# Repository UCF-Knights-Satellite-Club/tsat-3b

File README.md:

# tsat-3b
TSat-3B repository containing all kicads and guided parafoil descent code

- [`FlightController/`](FlightController/) - ESP32 guided parafoil flight controller (Arduino sketch). See its README.
- [`PowerDistributionBoard/`](PowerDistributionBoard/) - power distribution board (KiCad 10): schematic, PCB, Gerbers, BOM.

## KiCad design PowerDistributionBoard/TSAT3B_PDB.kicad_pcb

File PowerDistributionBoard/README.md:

# TSat-3B Power Distribution Board

<p align="center">
  <b>Rev B: review draft</b> &nbsp;·&nbsp; 55 × 40 mm &nbsp;·&nbsp; 2-layer, 1.6 mm &nbsp;·&nbsp; KiCad 10
</p>

This board takes the battery and makes every rail TSat-3B needs. It powers the flight computer, the radio, the GPS, the IMU,
the SD card and the parafoil servo, and it switches the cutter channel.

| Top | Bottom |
|:---:|:---:|
|  |  |

📄 **Schematic:** [PDF](docs/TSAT3B_PDB_schematic.pdf) · [SVG](docs/TSAT3B_PDB_schematic.svg)
&nbsp;&nbsp;🧾 **BOM:** [CSV](bom/TSAT3B_PDB_BOM.csv)
&nbsp;&nbsp;🏭 **Fabrication:** [Gerbers + drill (zip)](fabrication/TSAT3B_PDB_gerbers.zip)

## Power tree

```
 Battery (J1, XT30)
   │
   ├─ Q3 AO4407A P-MOSFET load switch ◄── SW1 slide switch (gate control only, R12/R13)
   │
   └─ D1 SS54 reverse-polarity diode ──► VBUS
        │
        ├─ U1 SY8105 buck ───────► +5V   (73.2k / 10k  → 4.99 V)
        │     └─ U3 TLV1117LV33 ─► +3V3
        │
        ├─ U2 SY8105 buck ───────► VSERVO (73.2k / 8.2k → 5.96 V)
        │
        └─ J2 ARM LINK jumper ───► CUT_PWR ──► J11 cutter (Q1 AO3400A low-side switch)
```

Each rail (+5V, +3V3, VSERVO) has a green indicator LED.

## Connectors

| Ref | Name | Pins | Notes |
|---|---|---|---|
| J1 | BATTERY | XT30 | Battery input |
| J2 | ARM LINK | 2 × 2.54 mm | Jumper links VBUS → CUT_PWR to arm the cutter |
| J3 | PICO | +5V, GND | |
| J4 | LoRa | +3V3, GND | |
| J5 | GPS | +3V3, GND | |
| J6 | IMU | +3V3, GND | |
| J7 | SD CARD | +3V3, GND | |
| J8 | SERVO 1 | VSERVO, PWM, GND | JST PH 3-pin |
| J9 | ESP32 interface | +5V, GND, CUT1_CMD, SERVO1_PWM | 4 × 2.54 mm |
| J11 | CUTTER 1 | CUT_PWR, switched drain | XT30 |

## Bill of materials

42 parts, 25 line items. MPNs are in the [BOM CSV](bom/TSAT3B_PDB_BOM.csv).

| Qty | Refs | Part | Value / MPN |
|---:|---|---|---|
| 2 | U1, U2 | Buck regulator, Silergy | SY8105IADC |
| 1 | U3 | 3.3 V LDO, TI | TLV1117LV33DCYR |
| 1 | Q3 | P-MOSFET load switch, AOS | AO4407A |
| 1 | Q1 | N-MOSFET cutter switch, AOS | AO3400A |
| 1 | D1 | Schottky diode | SS54SMB |
| 2 | L1, L2 | Inductor, TDK | 2.2 µH SPM5030VT-2R2M-D |
| 6 | C1, C2, C4, C6–C8 | Capacitor 0805 | 22 µF 25 V |
| 3 | C3, C5, C9 | Capacitor 0603 | 100 nF 50 V |
| 11 | R1–R9, R12, R13 | Resistors 0603 | 73.2k, 10k, 8.2k, 1k, 100R |
| 3 | D2–D4 | LED 0603 | Green |
| 1 | SW1 | Slide switch | MSS22D18G2 |
| 2 | J1, J11 | Connector | XT30UPB-M |
| 8 | J2–J9 | Headers | 2.54 mm / JST PH |

## Repository layout

```
PowerDistributionBoard/
├── TSAT3B_PDB.kicad_pro / .kicad_sch / .kicad_pcb   KiCad 10 project
├── TSAT3B.kicad_sym, TSAT3B.pretty/                 project symbol + footprint library
├── fp-lib-table, sym-lib-table                      point at the local library (${KIPRJMOD})
├── fabrication/                                     Gerbers, drill files, job file, zip
├── bom/                                             BOM (CSV)
└── docs/                                            schematic PDF/SVG and 3D renders
```

Open `TSAT3B_PDB.kicad_pro` in **KiCad 10 or newer**; KiCad 9 can't read these files. The custom parts in
`TSAT3B.pretty` (XT30, slide switch, inductors, SY8105) have no 3D models yet, so they show as bare pads in the renders.

## Status: open items before fabrication

Rev B is still a **review draft**. These come from the review notes in the schematic:

- [ ] Battery voltage/specification. The design assumes a supply that suits the 6 V buck and the switch's ≤12 V rating.
- [ ] Cutter: resistance/current, pulse duration and Q1 thermal/SOA check.
- [ ] Q3 and D1 current, inrush and dissipation, once battery and load data are known.
- [ ] VSERVO at 5.96 V: confirm it suits the servos.
- [ ] Verify land patterns: SY8105 (TSOT23-6), TDK inductor, XT30 (also polarity), and the slide switch contacts.
- [ ] Confirm harness polarity on all 2-pin headers, and the servo pin order (1 VSERVO, 2 PWM, 3 GND).
- [ ] Arming-link topology (VBUS → CUT_PWR): verify against the source design.
- [ ] Cross-check with the flight code: the parafoil controller in [`../FlightController`](../FlightController) drives
      **two** winch servos (left and right lines). This board has one servo header (J8) and one PWM line on J9.

Check results (KiCad 10.0.7):
- **DRC:** 0 unconnected pads and no clearance errors.
- **Parity:** the 4 mounting holes exist only on the PCB.
- **ERC:** 3 "power pin not driven" errors, which usually just need `PWR_FLAG` symbols on GND / VBAT_RAW / VBUS.

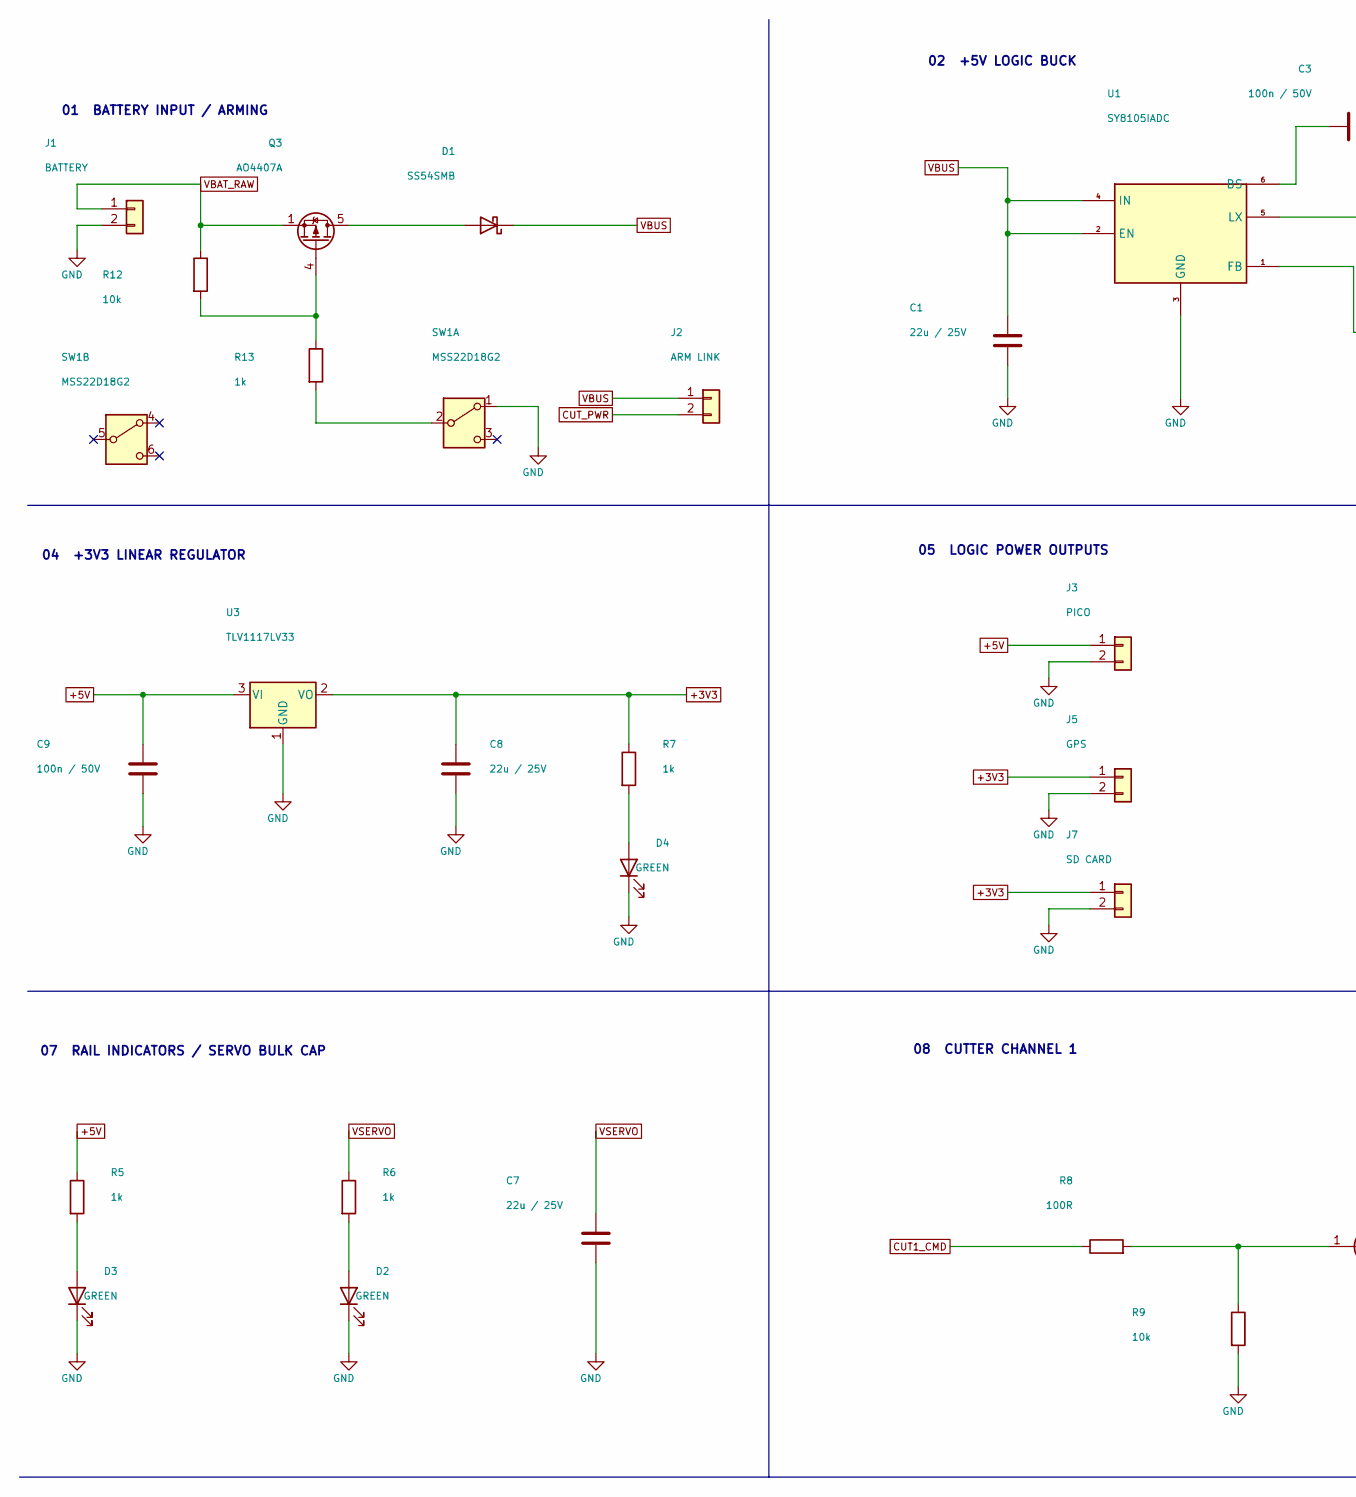
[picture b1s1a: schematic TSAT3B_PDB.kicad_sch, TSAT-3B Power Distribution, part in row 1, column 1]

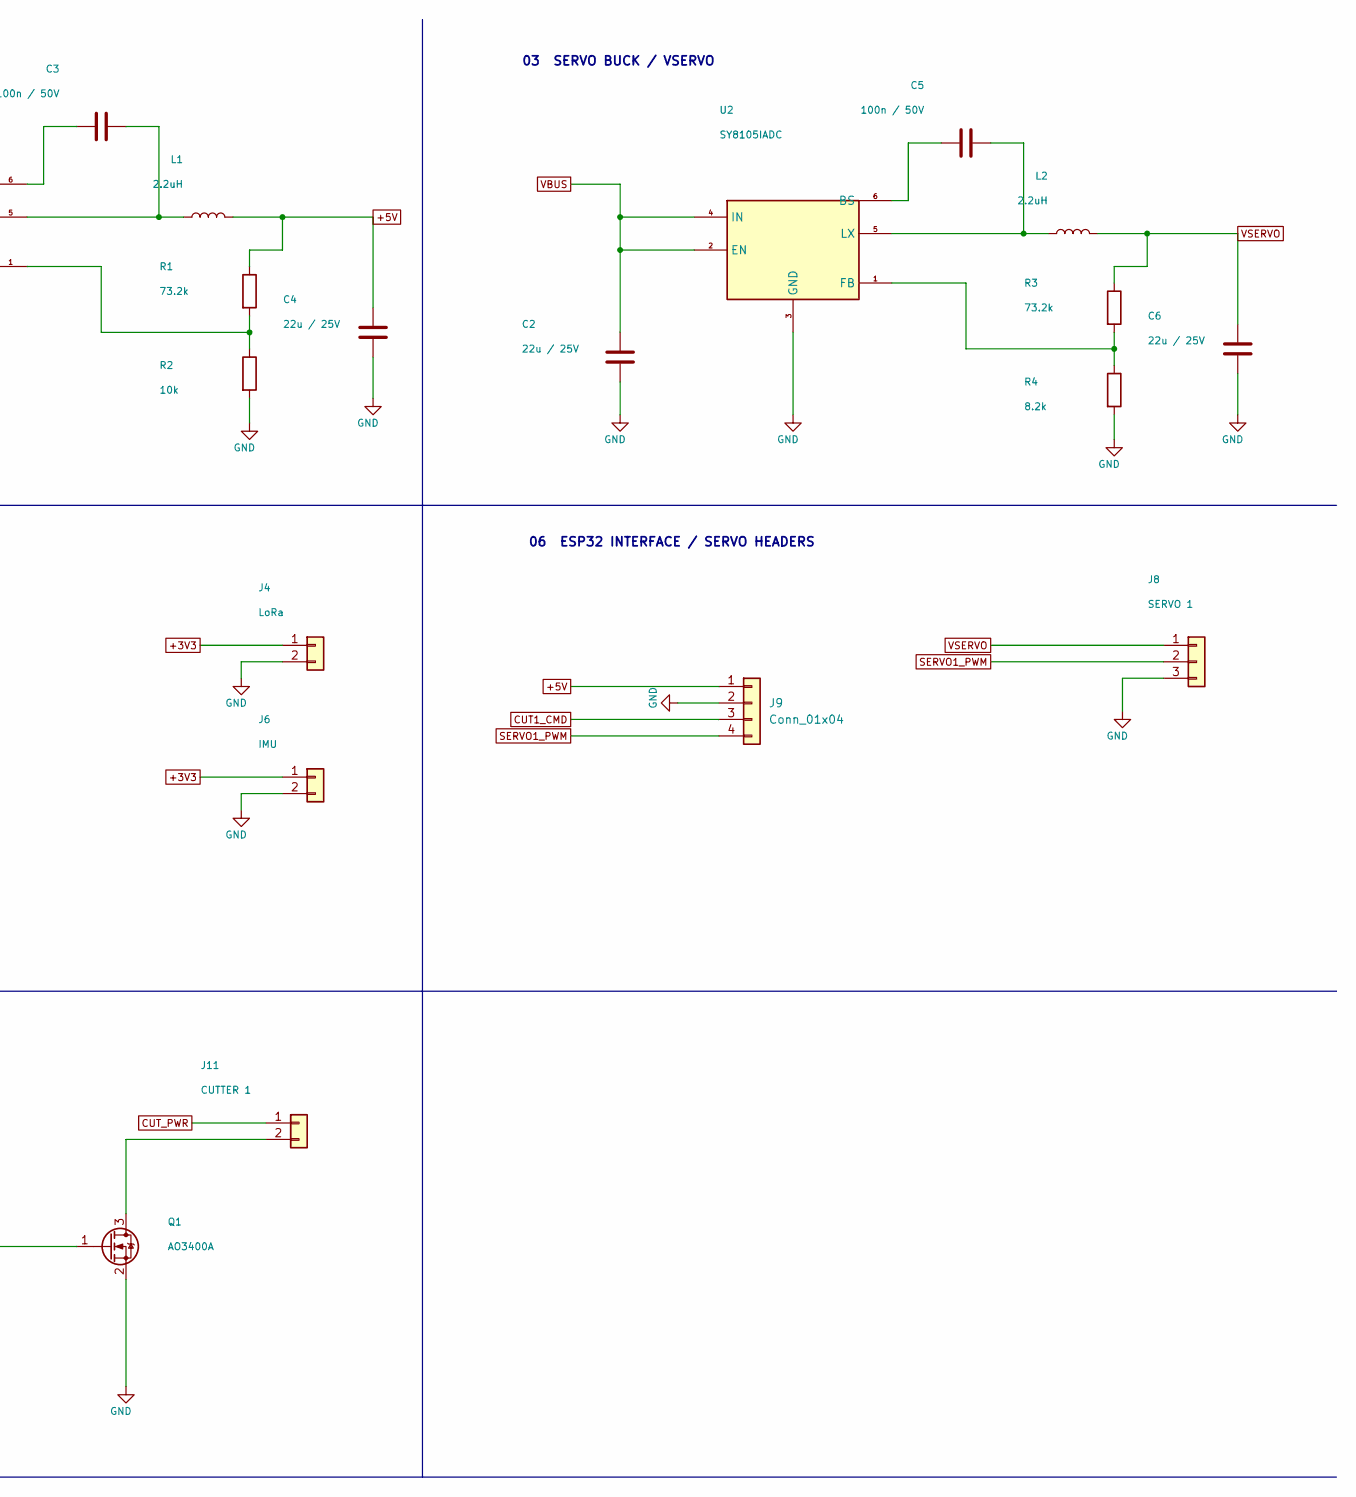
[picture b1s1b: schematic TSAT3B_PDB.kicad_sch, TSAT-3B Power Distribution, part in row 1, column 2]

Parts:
C1, C2, C4, C6, C7, C8: 22u / 25V; C_0805_2012Metric; MPN TCC0805X5R226M250FT
C3, C5, C9: 100n / 50V; C_0603_1608Metric; MPN 0603B104K500NT
D1: SS54SMB; D_SMB; MPN SS54SMB
D2, D3, D4: GREEN; LED_0603_1608Metric; MPN YLED0603G
J1: BATTERY; AMASS_XT30UPB-M_P1_Positive; MPN XT30UPB-M
J2: ARM LINK; PinHeader_1x02_P2.54mm_Vertical; MPN PZ254V-11-02P
J3: PICO; PinHeader_1x02_P2.54mm_Vertical; MPN PZ254V-11-02P
J4: LoRa; PinHeader_1x02_P2.54mm_Vertical; MPN PZ254V-11-02P
J5: GPS; PinHeader_1x02_P2.54mm_Vertical; MPN PZ254V-11-02P
J6: IMU; PinHeader_1x02_P2.54mm_Vertical; MPN PZ254V-11-02P
J7: SD CARD; PinHeader_1x02_P2.54mm_Vertical; MPN PZ254V-11-02P
J8: SERVO 1; JST_PH_B3B-PH-K_1x03_P2.00mm_Vertical; MPN 2.54-1*3P
J9: Conn_01x04; PinHeader_1x04_P2.54mm_Vertical
J11: CUTTER 1; AMASS_XT30UPB-M_P1_Positive; MPN XT30UPB-M
L1, L2: 2.2uH; L_TDK_SPM5030VT; MPN SPM5030VT-2R2M-D
Q1: AO3400A; SOT-23; MPN AO3400A
Q3: AO4407A; SOIC-8_3.9x4.9mm_P1.27mm; MPN AO4407A
R1, R3: 73.2k; R_0603_1608Metric; MPN 0603WAF7322T5E
R2, R9, R12: 10k; R_0603_1608Metric; MPN CRGCQ0603F10K
R4: 8.2k; R_0603_1608Metric; MPN FRQ0603F8201TS
R5, R6, R7, R13: 1k; R_0603_1608Metric; MPN 1RC0603F1001
R8: 100R; R_0603_1608Metric; MPN CR0603JA0101G
SW1: MSS22D18G2; SW_SHOUHAN_MSS22D18G2
U1, U2: SY8105IADC; SY8105IADC_TSOT23_6_MfrLand; MPN SY8105IADC
U3: TLV1117LV33; SOT-223-3_TabPin2; MPN TLV1117LV33DCYR

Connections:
+3V3: C8.1, J4.1, J5.1, J6.1, J7.1, R7.1, U3.2 (VO)
+5V: C4.1, C9.1, J3.1, J9.1, L1.2, R1.1, R5.1, U3.3 (VI)
CUT1_CMD: J9.3, R8.1
CUT_PWR: J2.2, J11.1
GND: C1.2, C2.2, C4.2, C6.2, C7.2, C8.2, C9.2, D2.1 (K), D3.1 (K), D4.1 (K), J1.2, J3.2, J4.2, J5.2, J6.2, J7.2, J8.3, J9.2, Q1.2 (S), R2.2, R4.2, R9.2, SW1.1 (A), U1.3 (GND), U2.3 (GND), U3.1 (GND)
unnamed: D1.2 (A), Q3.5 (D), Q3.6 (D), Q3.7 (D), Q3.8 (D)
unnamed: D2.2 (A), R6.2
unnamed: D3.2 (A), R5.2
unnamed: D4.2 (A), R7.2
unnamed: J11.2, Q1.3 (D)
unnamed: Q1.1 (G), R8.2, R9.1
unnamed: Q3.4 (G), R12.2, R13.1
unnamed: R13.2, SW1.2 (B)
unnamed: C3.1, U1.6 (BS)
unnamed: R1.2, R2.1, U1.1 (FB)
unnamed: C3.2, L1.1, U1.5 (LX)
unnamed: C5.1, U2.6 (BS)
unnamed: R3.2, R4.1, U2.1 (FB)
unnamed: C5.2, L2.1, U2.5 (LX)
SERVO1_PWM: J8.2, J9.4
VBAT_RAW: J1.1, Q3.1 (S), Q3.2 (S), Q3.3 (S), R12.1
VBUS: C1.1, C2.1, D1.1 (K), J2.1, U1.2 (EN), U1.4 (IN), U2.2 (EN), U2.4 (IN)
VSERVO: C6.1, C7.1, J8.1, L2.2, R3.1, R6.1

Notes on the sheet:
06 ESP32 INTERFACE / SERVO HEADERS
03 SERVO BUCK / VSERVO
04 +3V3 LINEAR REGULATOR
02 +5V LOGIC BUCK
01 BATTERY INPUT / ARMING
08 CUTTER CHANNEL 1
07 RAIL INDICATORS / SERVO BULK CAP
05 LOGIC POWER OUTPUTS

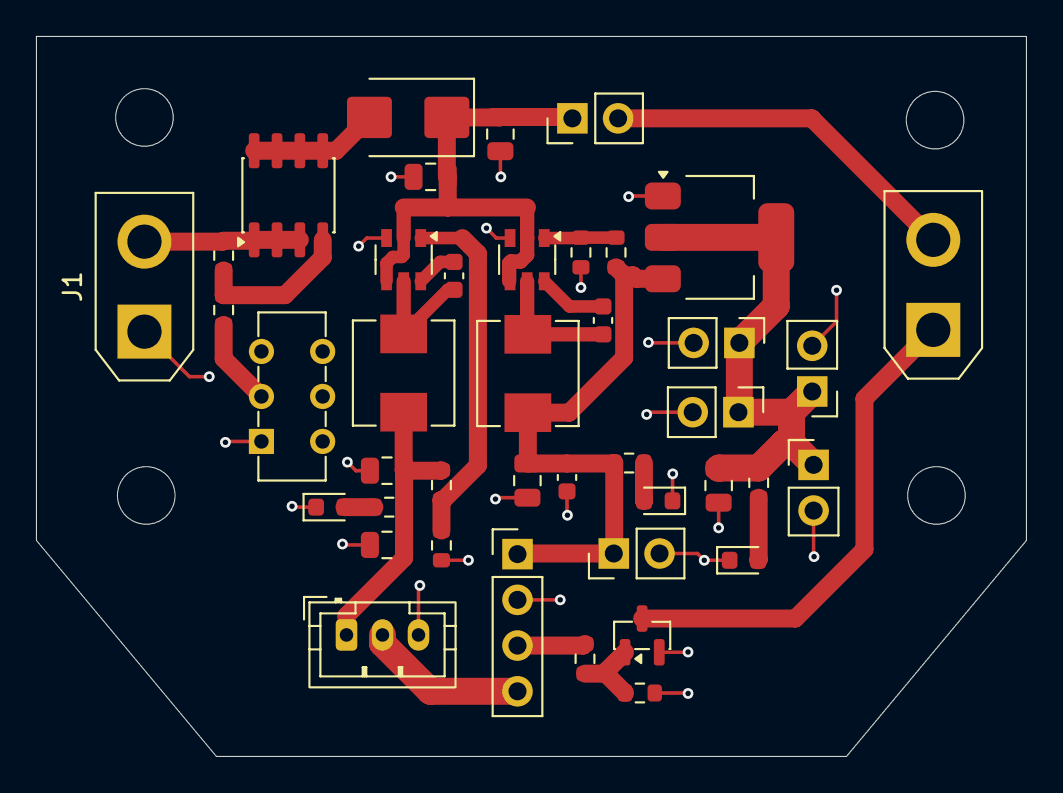
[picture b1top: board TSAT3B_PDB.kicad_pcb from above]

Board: 2 copper layers, 55.0 x 40.0 mm, 42 parts (0 on the bottom side), 23 nets.

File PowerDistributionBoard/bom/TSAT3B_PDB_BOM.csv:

"Reference","Value","Footprint","MPN","Manufacturer","Qty"
"C1,C2,C4,C6-C8","22u / 25V","Capacitor_SMD:C_0805_2012Metric","TCC0805X5R226M250FT","CCTC","6"
"C3,C5,C9","100n / 50V","Capacitor_SMD:C_0603_1608Metric","0603B104K500NT","FH","3"
"D1","SS54SMB","Diode_SMD:D_SMB","SS54SMB","BORN","1"
"D2-D4","GREEN","LED_SMD:LED_0603_1608Metric","YLED0603G","YONGYUTAI","3"
"J1","BATTERY","TSAT3B:AMASS_XT30UPB-M_P1_Positive","XT30UPB-M","","1"
"J2","ARM LINK","Connector_PinHeader_2.54mm:PinHeader_1x02_P2.54mm_Vertical","PZ254V-11-02P","","1"
"J3","PICO","Connector_PinHeader_2.54mm:PinHeader_1x02_P2.54mm_Vertical","PZ254V-11-02P","","1"
"J4","LoRa","Connector_PinHeader_2.54mm:PinHeader_1x02_P2.54mm_Vertical","PZ254V-11-02P","","1"
"J5","GPS","Connector_PinHeader_2.54mm:PinHeader_1x02_P2.54mm_Vertical","PZ254V-11-02P","","1"
"J6","IMU","Connector_PinHeader_2.54mm:PinHeader_1x02_P2.54mm_Vertical","PZ254V-11-02P","","1"
"J7","SD CARD","Connector_PinHeader_2.54mm:PinHeader_1x02_P2.54mm_Vertical","PZ254V-11-02P","","1"
"J8","SERVO 1","Connector_JST:JST_PH_B3B-PH-K_1x03_P2.00mm_Vertical","2.54-1*3P","","1"
"J9","Conn_01x04","Connector_PinHeader_2.54mm:PinHeader_1x04_P2.54mm_Vertical","","","1"
"J11","CUTTER 1","TSAT3B:AMASS_XT30UPB-M_P1_Positive","XT30UPB-M","","1"
"L1,L2","2.2uH","TSAT3B:L_TDK_SPM5030VT","SPM5030VT-2R2M-D","TDK","2"
"Q1","AO3400A","Package_TO_SOT_SMD:SOT-23","AO3400A","Alpha & Omega Semiconductor","1"
"Q3","AO4407A","Package_SO:SOIC-8_3.9x4.9mm_P1.27mm","AO4407A","Alpha & Omega Semiconductor","1"
"R1,R3","73.2k","Resistor_SMD:R_0603_1608Metric","0603WAF7322T5E","","2"
"R2,R9,R12","10k","Resistor_SMD:R_0603_1608Metric","CRGCQ0603F10K","TE Connectivity","3"
"R4","8.2k","Resistor_SMD:R_0603_1608Metric","FRQ0603F8201TS","","1"
"R5-R7,R13","1k","Resistor_SMD:R_0603_1608Metric","1RC0603F1001","","4"
"R8","100R","Resistor_SMD:R_0603_1608Metric","CR0603JA0101G","","1"
"SW1","MSS22D18G2","TSAT3B:SW_SHOUHAN_MSS22D18G2","MSS22D18G2","SHOU HAN","1"
"U1,U2","SY8105IADC","TSAT3B:SY8105IADC_TSOT23_6_MfrLand","SY8105IADC","Silergy Corp","2"
"U3","TLV1117LV33","Package_TO_SOT_SMD:SOT-223-3_TabPin2","TLV1117LV33DCYR","Texas Instruments","1"
